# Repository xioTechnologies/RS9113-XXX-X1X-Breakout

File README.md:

RS9113-XXX-X1X-Breakout
=======================

Breakboard for the Redpine Signals [RS9113-XXX-X1X](http://www.redpinesignals.com/Modules/Internet_of_Things/Connection_Family/RS9113.php) Wi-Fi module.  Includes pull-down resistors as per datasheet.

The silkscreen overlaps copper pads with the intention that this is corrected by the PCB fabrication supplier.

Photo (with connections for UART)
---------------------------------

PCB Preview from OSH Park
-------------------------

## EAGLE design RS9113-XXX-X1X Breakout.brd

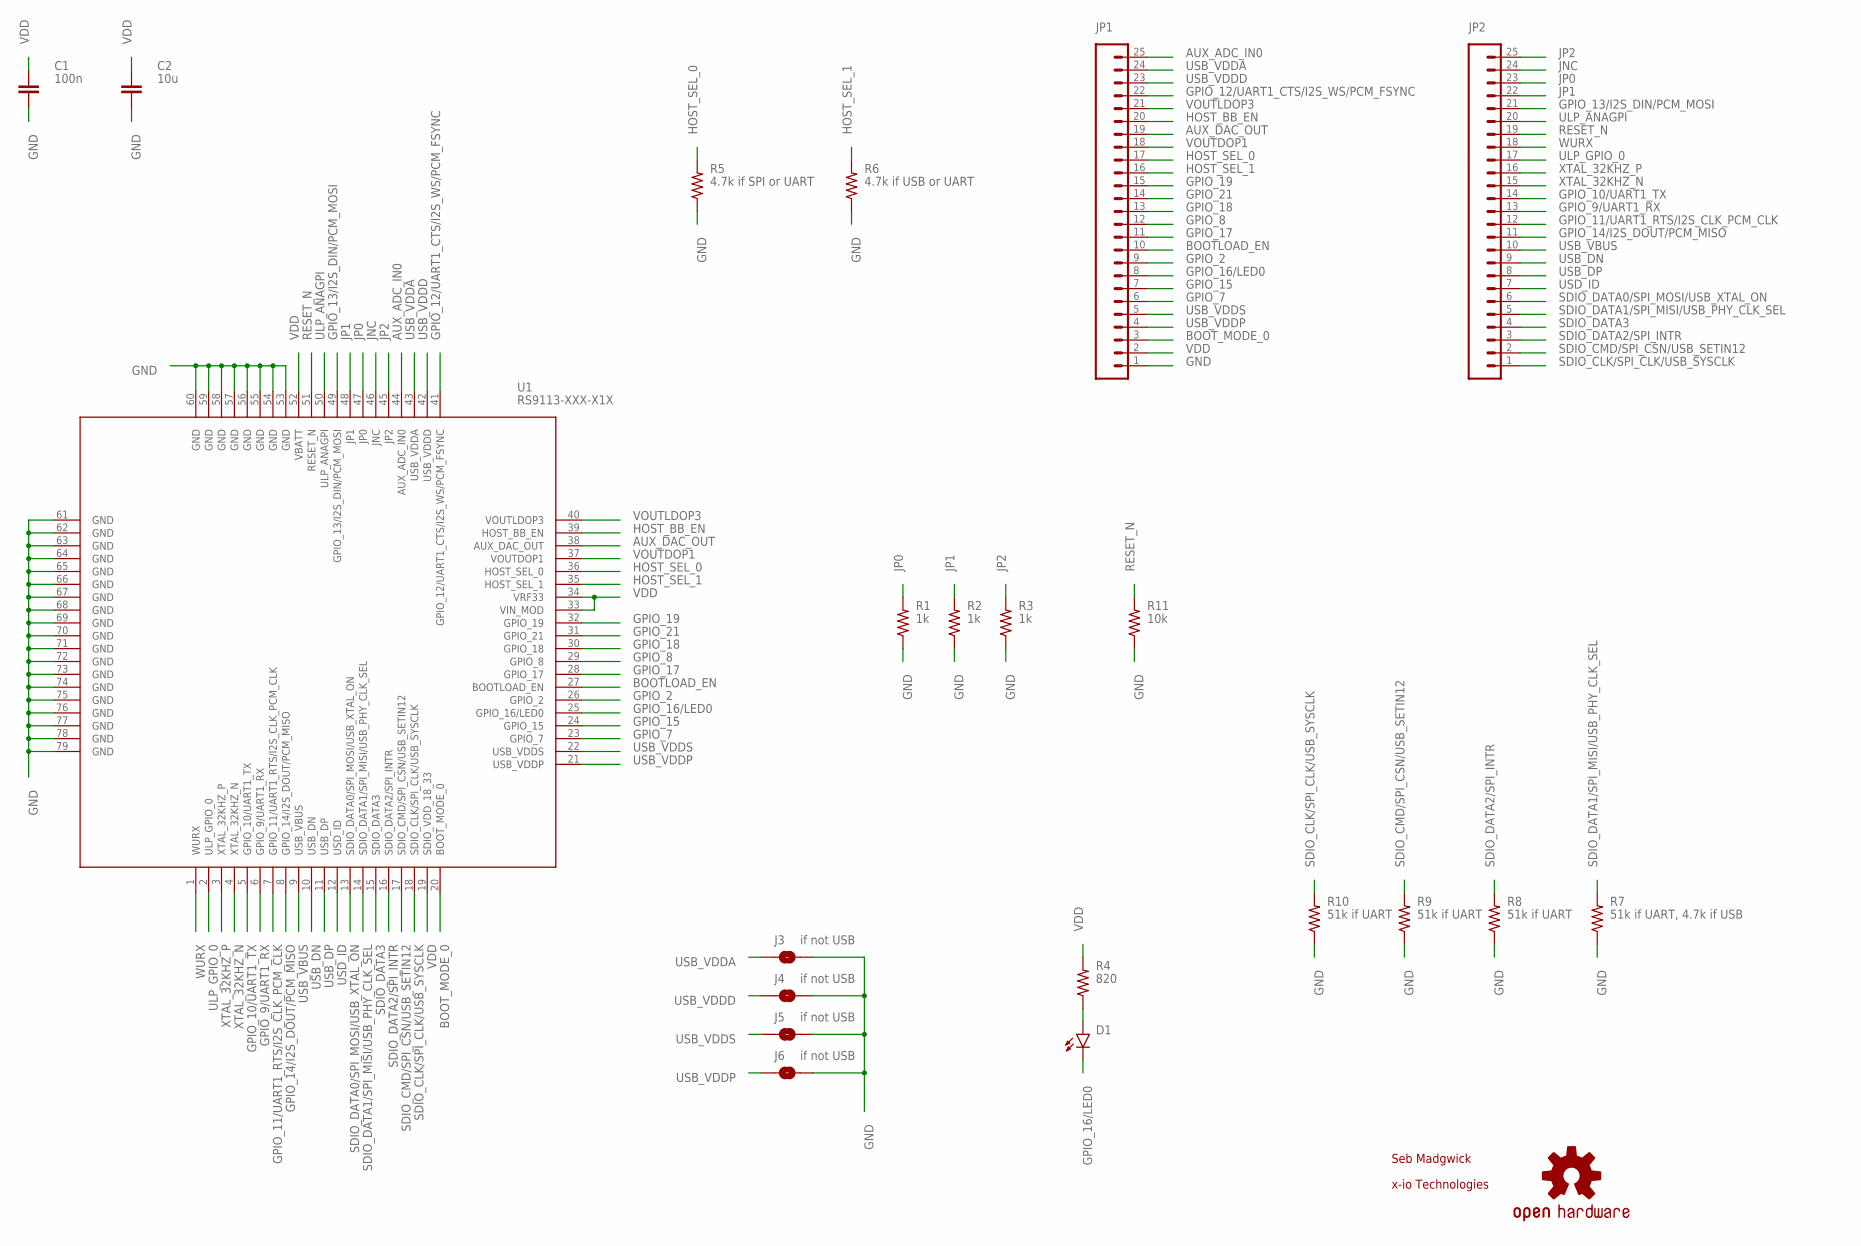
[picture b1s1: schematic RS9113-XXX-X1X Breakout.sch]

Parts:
C1: 100n; 0603-CAP
C2: 10u; 0603-CAP
D1: GREEN; LED-0603
J3, J4, J5, J6: if not USB; SJ_2S-NO
JP1, JP2: M25PTH; 1X25
LOGO1: OSHW-LOGOS; OSHW-LOGO-S
R1, R2, R3: 1k; 0603-RES
R4: 820; 0603-RES
R5: 4.7k if SPI or UART; 0603-RES
R6: 4.7k if USB or UART; 0603-RES
R7: 51k if UART, 4.7k if USB; 0603-RES
R8, R9, R10: 51k if UART; 0603-RES
R11: 10k; 0603-RES
U1: RS9113-XXX-X1X

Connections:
AUX_ADC_IN0: JP1.25, U1.44 (AUX_ADC_IN0)
AUX_DAC_OUT: JP1.19, U1.38 (AUX_DAC_OUT)
BOOTLOAD_EN: JP1.10, U1.27 (BOOTLOAD_EN)
BOOT_MODE_0: JP1.3, U1.20 (BOOT_MODE_0)
GND: C1.2, C2.2, J3.1, J4.1, J5.1, J6.1, JP1.1, R1.1, R2.1, R3.1, R5.1, R6.1, R7.1, R8.1, R9.1, R10.1, R11.1, U1.53 (GND), U1.54 (GND), U1.55 (GND), U1.56 (GND), U1.57 (GND), U1.58 (GND), U1.59 (GND), U1.60 (GND), U1.61 (GND), U1.62 (GND), U1.63 (GND), U1.64 (GND), U1.65 (GND), U1.66 (GND), U1.67 (GND), U1.68 (GND), U1.69 (GND), U1.70 (GND), U1.71 (GND), U1.72 (GND), U1.73 (GND), U1.74 (GND), U1.75 (GND), U1.76 (GND), U1.77 (GND), U1.78 (GND), U1.79 (GND)
GPIO_2: JP1.9, U1.26 (GPIO_2)
GPIO_7: JP1.6, U1.23 (GPIO_7)
GPIO_8: JP1.12, U1.29 (GPIO_8)
GPIO_9/UART1_RX: JP2.13, U1.6 (GPIO_9/UART1_RX)
GPIO_10/UART1_TX: JP2.14, U1.5 (GPIO_10/UART1_TX)
GPIO_11/UART1_RTS/I2S_CLK_PCM_CLK: JP2.12, U1.7 (GPIO_11/UART1_RTS/I2S_CLK_PCM_CLK)
GPIO_12/UART1_CTS/I2S_WS/PCM_FSYNC: JP1.22, U1.41 (GPIO_12/UART1_CTS/I2S_WS/PCM_FSYNC)
GPIO_13/I2S_DIN/PCM_MOSI: JP2.21, U1.49 (GPIO_13/I2S_DIN/PCM_MOSI)
GPIO_14/I2S_DOUT/PCM_MISO: JP2.11, U1.8 (GPIO_14/I2S_DOUT/PCM_MISO)
GPIO_15: JP1.7, U1.24 (GPIO_15)
GPIO_16/LED0: D1.C, JP1.8, U1.25 (GPIO_16/LED0)
GPIO_17: JP1.11, U1.28 (GPIO_17)
GPIO_18: JP1.13, U1.30 (GPIO_18)
GPIO_19: JP1.15, U1.32 (GPIO_19)
GPIO_21: JP1.14, U1.31 (GPIO_21)
HOST_BB_EN: JP1.20, U1.39 (HOST_BB_EN)
HOST_SEL_0: JP1.17, R5.2, U1.36 (HOST_SEL_0)
HOST_SEL_1: JP1.16, R6.2, U1.35 (HOST_SEL_1)
JNC: JP2.24, U1.46 (JNC)
JP0: JP2.23, R1.2, U1.47 (JP0)
JP1: JP2.22, R2.2, U1.48 (JP1)
JP2: JP2.25, R3.2, U1.45 (JP2)
unnamed: D1.A, R4.1
RESET_N: JP2.19, R11.2, U1.51 (RESET_N)
SDIO_CLK/SPI_CLK/USB_SYSCLK: JP2.1, R10.2, U1.18 (SDIO_CLK/SPI_CLK/USB_SYSCLK)
SDIO_CMD/SPI_CSN/USB_SETIN12: JP2.2, R9.2, U1.17 (SDIO_CMD/SPI_CSN/USB_SETIN12)
SDIO_DATA0/SPI_MOSI/USB_XTAL_ON: JP2.6, U1.13 (SDIO_DATA0/SPI_MOSI/USB_XTAL_ON)
SDIO_DATA1/SPI_MISI/USB_PHY_CLK_SEL: JP2.5, R7.2, U1.14 (SDIO_DATA1/SPI_MISI/USB_PHY_CLK_SEL)
SDIO_DATA2/SPI_INTR: JP2.3, R8.2, U1.16 (SDIO_DATA2/SPI_INTR)
SDIO_DATA3: JP2.4, U1.15 (SDIO_DATA3)
ULP_ANAGPI: JP2.20, U1.50 (ULP_ANAGPI)
ULP_GPIO_0: JP2.17, U1.2 (ULP_GPIO_0)
USB_DN: JP2.9, U1.10 (USB_DN)
USB_DP: JP2.8, U1.11 (USB_DP)
USB_VBUS: JP2.10, U1.9 (USB_VBUS)
USB_VDDA: J3.2, JP1.24, U1.43 (USB_VDDA)
USB_VDDD: J4.2, JP1.23, U1.42 (USB_VDDD)
USB_VDDP: J6.2, JP1.4, U1.21 (USB_VDDP)
USB_VDDS: J5.2, JP1.5, U1.22 (USB_VDDS)
USD_ID: JP2.7, U1.12 (USD_ID)
VDD: C1.1, C2.1, JP1.2, R4.2, U1.19 (SDIO_VDD_18_33), U1.33 (VIN_MOD), U1.34 (VRF33), U1.52 (VBATT)
VOUTDOP1: JP1.18, U1.37 (VOUTDOP1)
VOUTLDOP3: JP1.21, U1.40 (VOUTLDOP3)
WURX: JP2.18, U1.1 (WURX)
XTAL_32KHZ_N: JP2.15, U1.4 (XTAL_32KHZ_N)
XTAL_32KHZ_P: JP2.16, U1.3 (XTAL_32KHZ_P)

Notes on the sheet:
Seb Madgwick
x-io Technologies

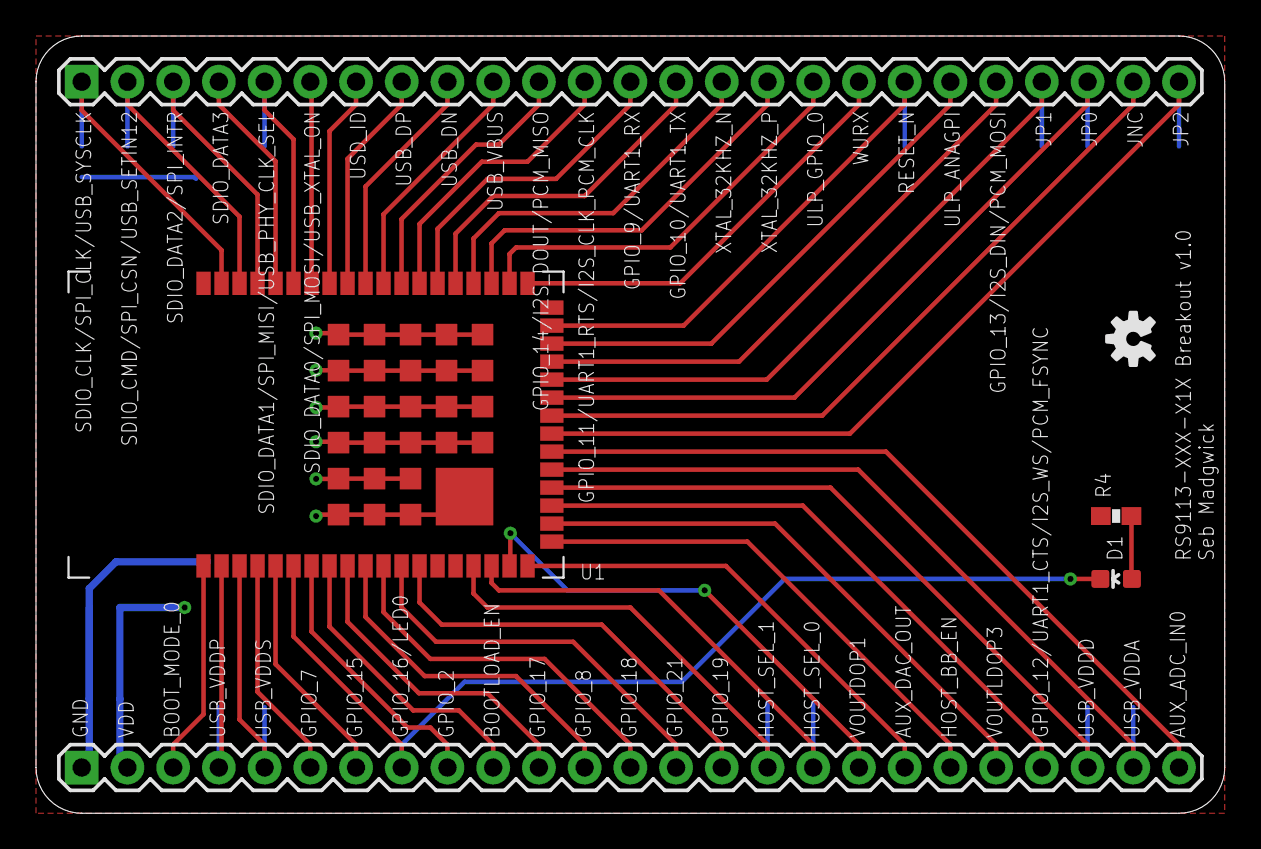
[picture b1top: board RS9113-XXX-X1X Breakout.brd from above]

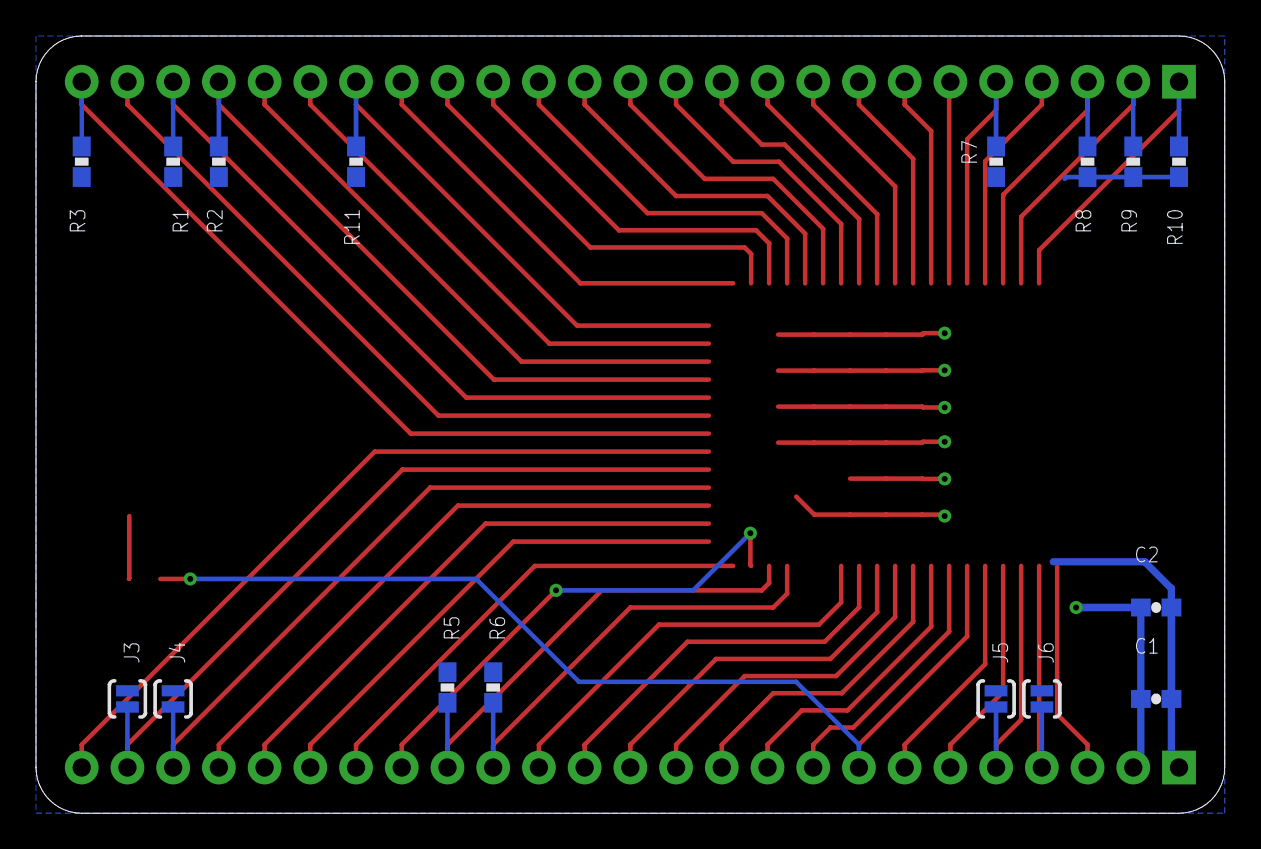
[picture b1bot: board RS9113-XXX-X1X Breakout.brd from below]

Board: 2 copper layers, 66.0 x 43.2 mm, 22 parts (16 on the bottom side), 51 nets.

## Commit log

2014-10-26 Commit project files
2015-02-12 Add photo

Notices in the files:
parts and their libraries:
SparkFun-Aesthetics: Licensing: Creative Commons ShareAlike 4.0 International - https://creativecommons.org/licenses/by-sa/4.0
